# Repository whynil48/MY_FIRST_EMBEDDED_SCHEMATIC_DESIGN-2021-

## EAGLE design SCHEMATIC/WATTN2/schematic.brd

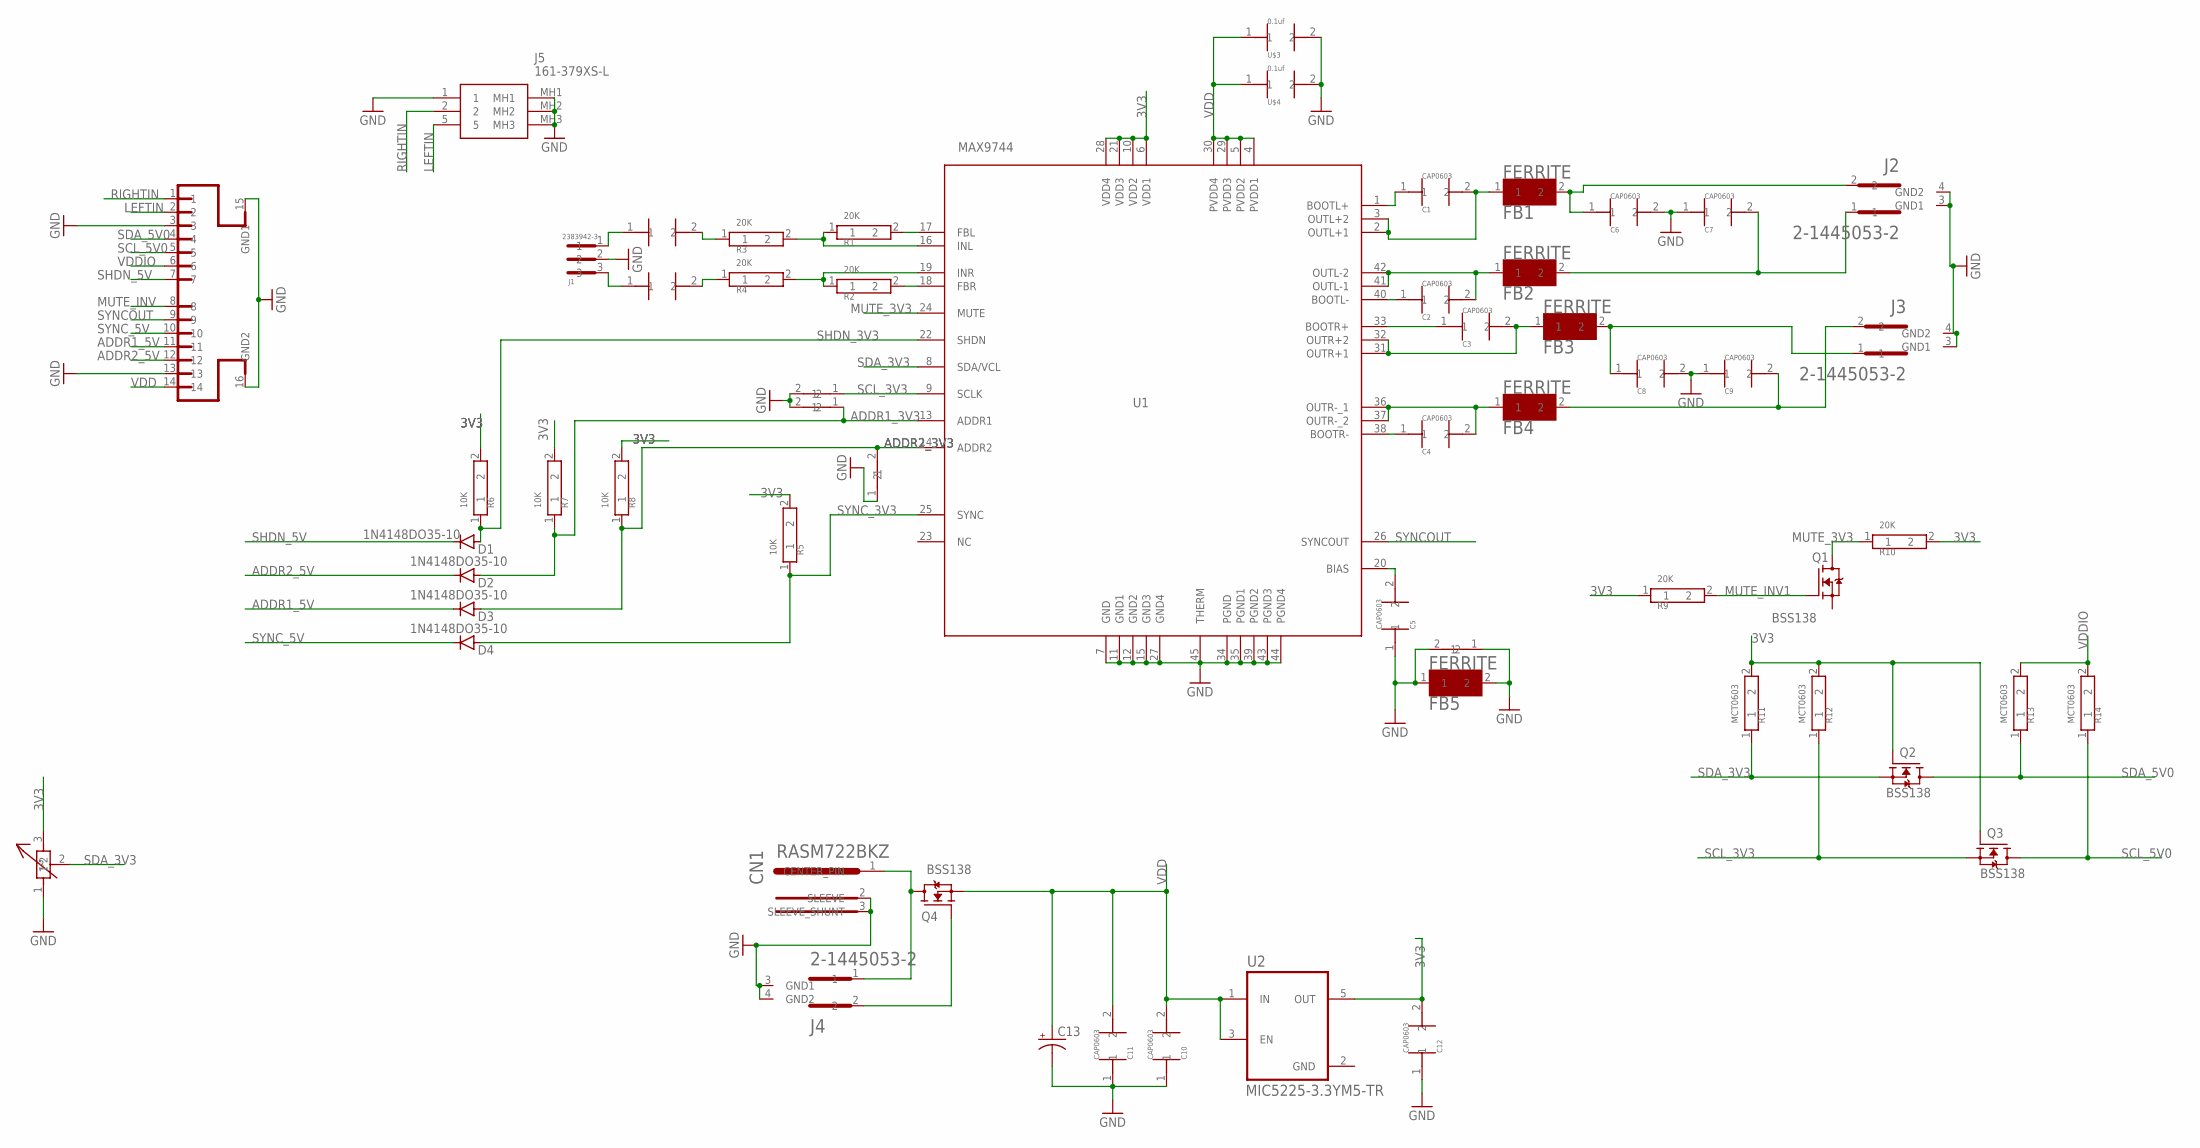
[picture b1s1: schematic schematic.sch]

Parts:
C1, C2, C3, C4, C5, C6, C7, C8, C9, C10, C11, C12: CAP0603
C13: CPOL-US085CS-1R; 085CS_1R
CN1: RASM722BKZ
D1, D2, D3, D4: 1N4148DO35-10; DO35-10
FB1, FB2, FB3, FB4, FB5: FERRITE
J1: 2383942-3
J2, J3, J4: 2-1445053-2
J5: 161-379XS-L; 161379XSL
J6: 4-794627-4
Q1, Q2, Q3, Q4: BSS138; SOT95P240X111-3N
R1, R2, R3, R4, R9, R10: 20K; MCT0603
R5, R6, R7, R8: 10K; MCT0603
R11, R12, R13, R14: MCT0603
SJ1, SJ2, SJ3, SJ4: QPC02SXGN-RC
U1: MAX9744
U2: MIC5225-3.3YM5-TR; SOT95P280X145-5N
U$1: 0.47uf; CAP0603
U$2: CAP0603
U$3, U$4: 0.1uf; CAP0603
VR1: T93YA223KT20

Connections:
3V3: C12.2, Q2.1 (G), Q3.1 (G), R6.2, R9.1, R10.2, R11.2, R12.2, U1.6 (VDD1), U1.10 (VDD2), U1.21 (VDD3), U1.28 (VDD4), U2.5 (OUT), VR1.3 (2)
ADDR1_3V3: D2.A, R7.1, SJ1.1, U1.13 (ADDR1)
ADDR1_5V: D3.C, J6.11
ADDR2_3V3: D3.A, R8.1, SJ2.2, U1.14 (ADDR2)
ADDR2_5V: D2.C, J6.12
GND: C5.1, C6.2, C7.1, C8.2, C9.1, C10.1, C11.1, C12.1, C13.-, CN1.2 (SLEEVE), CN1.3 (SLEEVE_SHUNT), FB5.1, FB5.2, J1.2, J2.3 (GND1), J2.4 (GND2), J3.3 (GND1), J3.4 (GND2), J4.3 (GND1), J4.4 (GND2), J5.1, J5.MH1, J5.MH2, J5.MH3, J6.3, J6.13, J6.15 (GND1), J6.16 (GND2), SJ1.2, SJ2.1, SJ3.2, SJ4.1, SJ4.2, U1.7 (GND), U1.11 (GND1), U1.12 (GND2), U1.15 (GND3), U1.27 (GND4), U1.34 (PGND), U1.35 (PGND1), U1.39 (PGND2), U1.43 (PGND3), U1.44 (PGND4), U1.45 (THERM), U2.2 (GND), U$3.2, U$4.2, VR1.1
LEFTIN: J5.5, J6.2
MUTE_3V3: Q1.3 (D), R10.1, U1.24 (MUTE)
MUTE_INV: J6.8
MUTE_INV1: Q1.1 (G), R9.2
unnamed: R1.2, U1.17 (FBL)
unnamed: R2.2, U1.18 (FBR)
unnamed: R1.1, R3.2, U1.16 (INL)
unnamed: R2.1, R4.2, U1.19 (INR)
unnamed: R4.1, U$2.2
unnamed: R3.1, U$1.2
unnamed: J1.1, U$1.1
unnamed: J1.3, U$2.1
unnamed: CN1.1 (CENTER_PIN), J4.1, Q4.3 (D)
unnamed: J4.2, Q4.1 (G)
unnamed: C1.2, FB1.1, U1.2 (OUTL+1), U1.3 (OUTL+2)
unnamed: C1.1, U1.1 (BOOTL+)
unnamed: C2.1, U1.40 (BOOTL-)
unnamed: C2.2, FB2.1, U1.41 (OUTL-1), U1.42 (OUTL-2)
unnamed: C3.1, U1.33 (BOOTR+)
unnamed: C3.2, FB3.1, U1.31 (OUTR+1), U1.32 (OUTR+2)
unnamed: C4.1, U1.38 (BOOTR-)
unnamed: C4.2, FB4.1, U1.36 (OUTR-_1), U1.37 (OUTR-_2)
unnamed: C6.1, FB1.2, J2.2
unnamed: C5.2, U1.20 (BIAS)
unnamed: C7.2, FB2.2, J2.1
unnamed: C8.1, FB3.2, J3.1
unnamed: C9.2, FB4.2, J3.2
RIGHTIN: J5.2, J6.1
SCL_3V3: Q3.2 (S), R12.1, SJ3.1, U1.9 (SCLK)
SCL_5V0: J6.5, Q3.3 (D), R14.1
SDA_3V3: Q2.2 (S), R11.1, U1.8 (SDA/VCL), VR1.2 (3)
SDA_5V0: J6.4, Q2.3 (D), R13.1
SHDN_3V3: D1.A, R6.1, U1.22 (SHDN)
SHDN_5V: D1.C, J6.7
SYNCOUT: J6.9, U1.26 (SYNCOUT)
SYNC_3V3: D4.A, R5.1, U1.25 (SYNC)
SYNC_5V: D4.C, J6.10
VDD: C10.2, C11.2, C13.+, J6.14, Q4.2 (S), U1.4 (PVDD1), U1.5 (PVDD2), U1.29 (PVDD3), U1.30 (PVDD4), U2.1 (IN), U2.3 (EN), U$3.1, U$4.1
VDDIO: J6.6, R13.2, R14.2

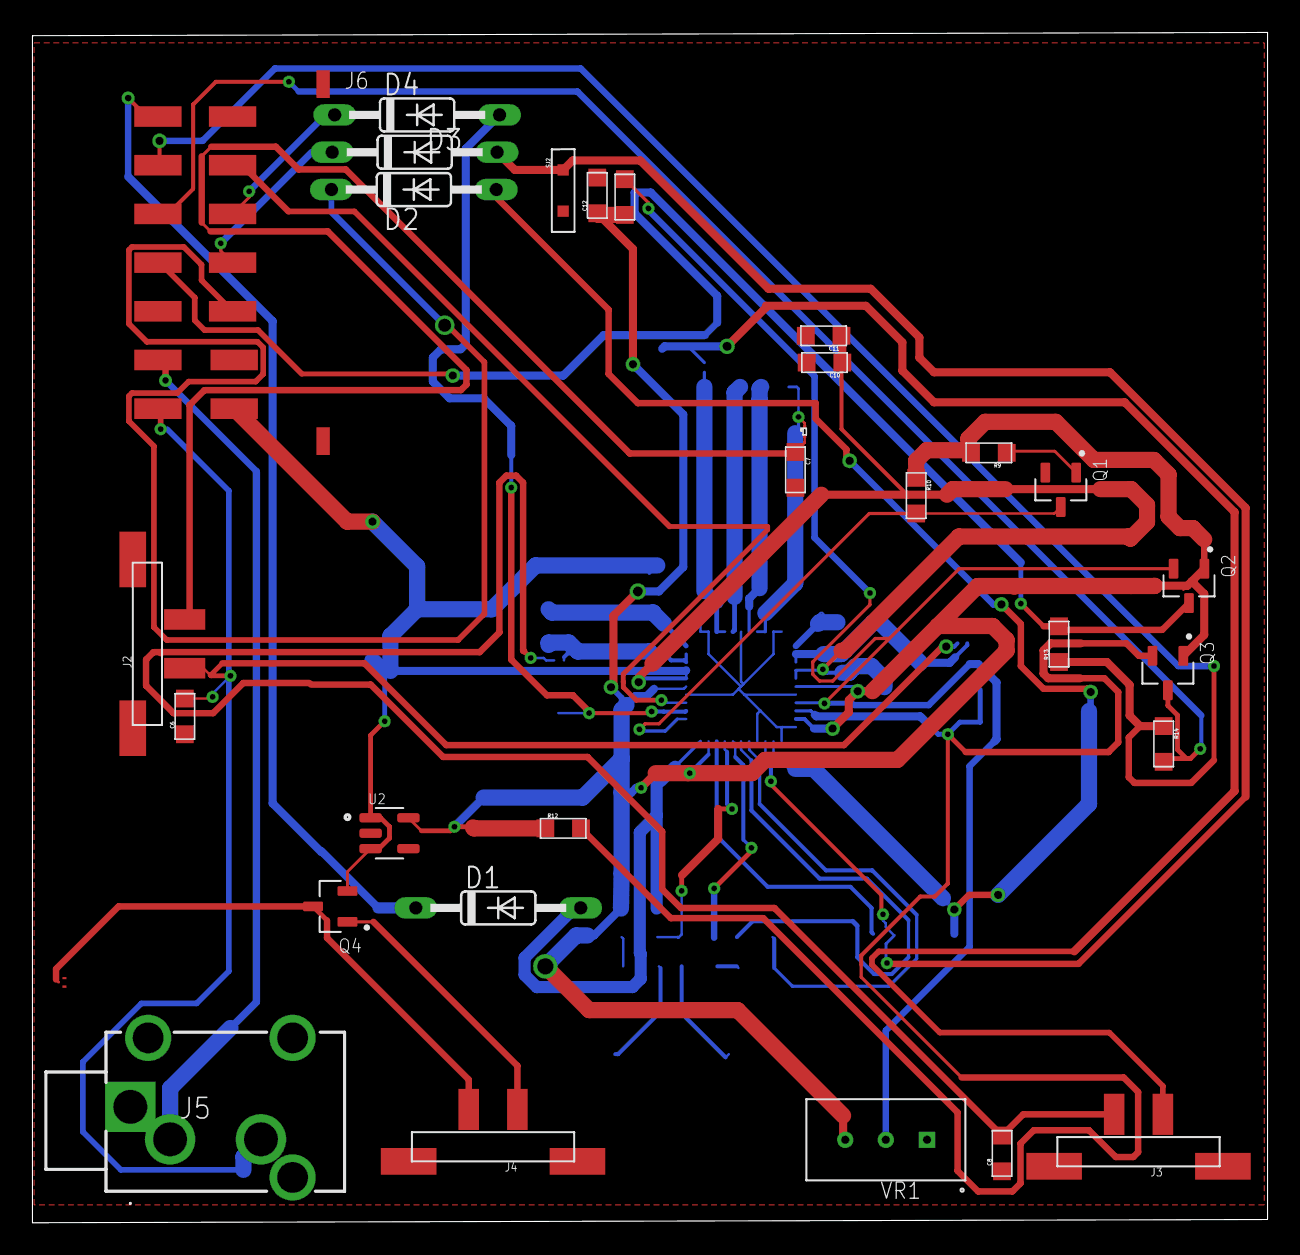
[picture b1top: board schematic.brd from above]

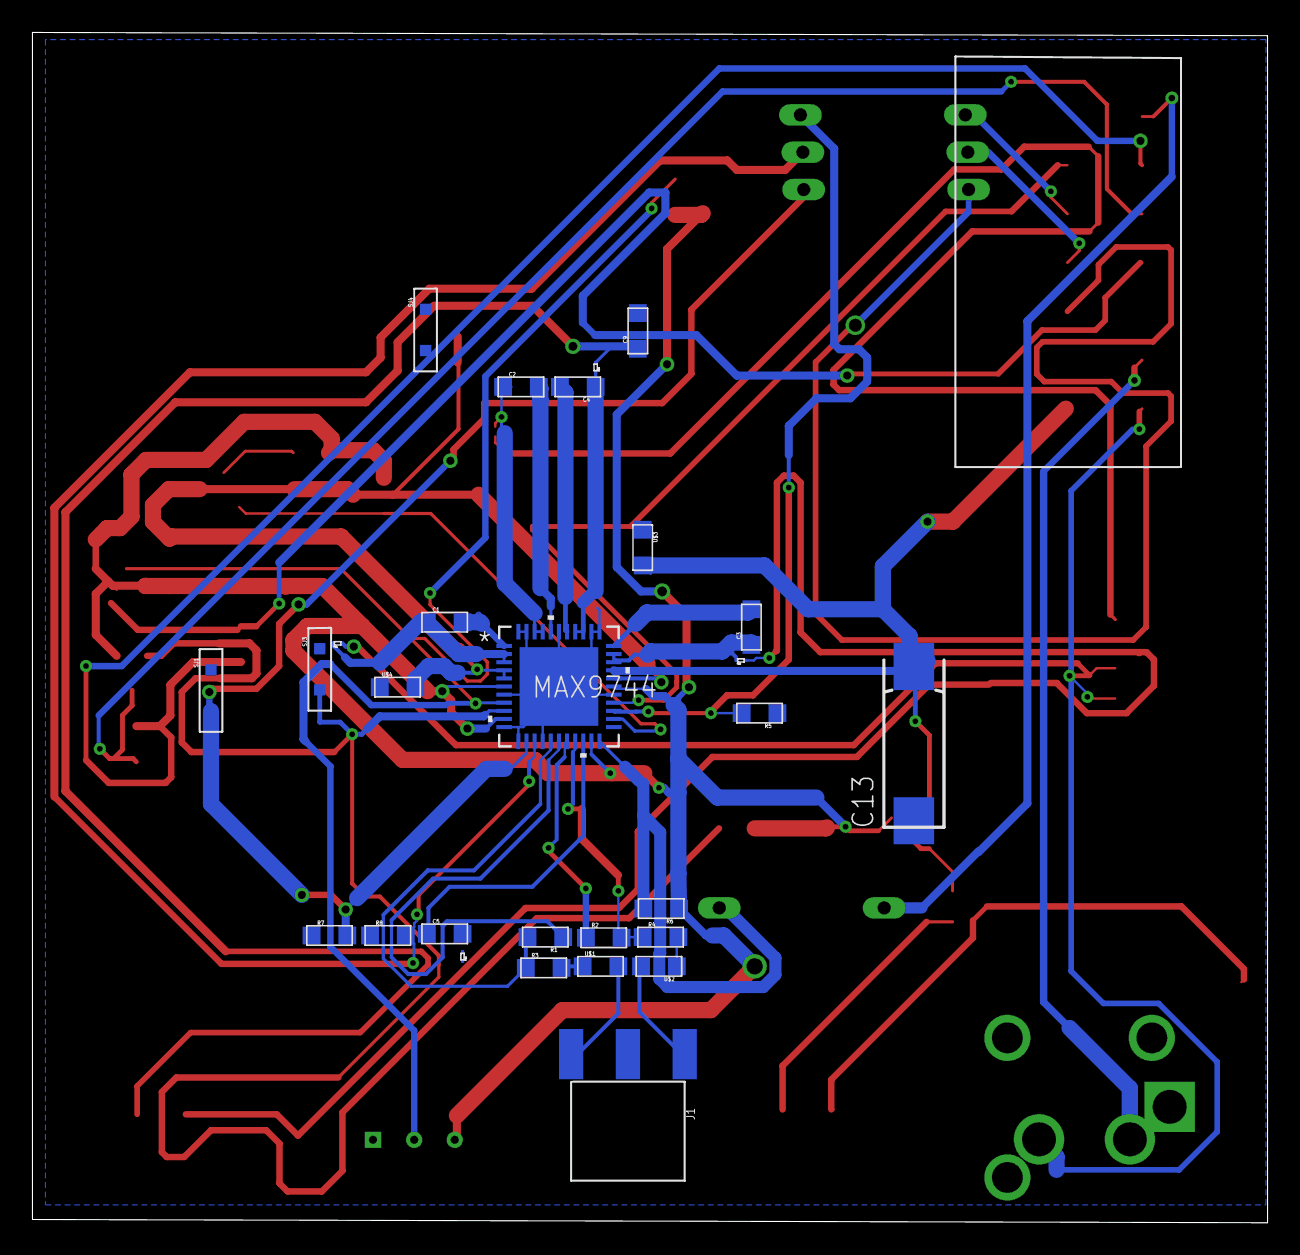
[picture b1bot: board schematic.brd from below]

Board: 2 copper layers, 76.1 x 73.3 mm, 58 parts (28 on the bottom side), 44 nets.

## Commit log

2024-05-13 Add files via upload
    Created a schematic for Smart_watch, PCB_DESIGN file is missing.
